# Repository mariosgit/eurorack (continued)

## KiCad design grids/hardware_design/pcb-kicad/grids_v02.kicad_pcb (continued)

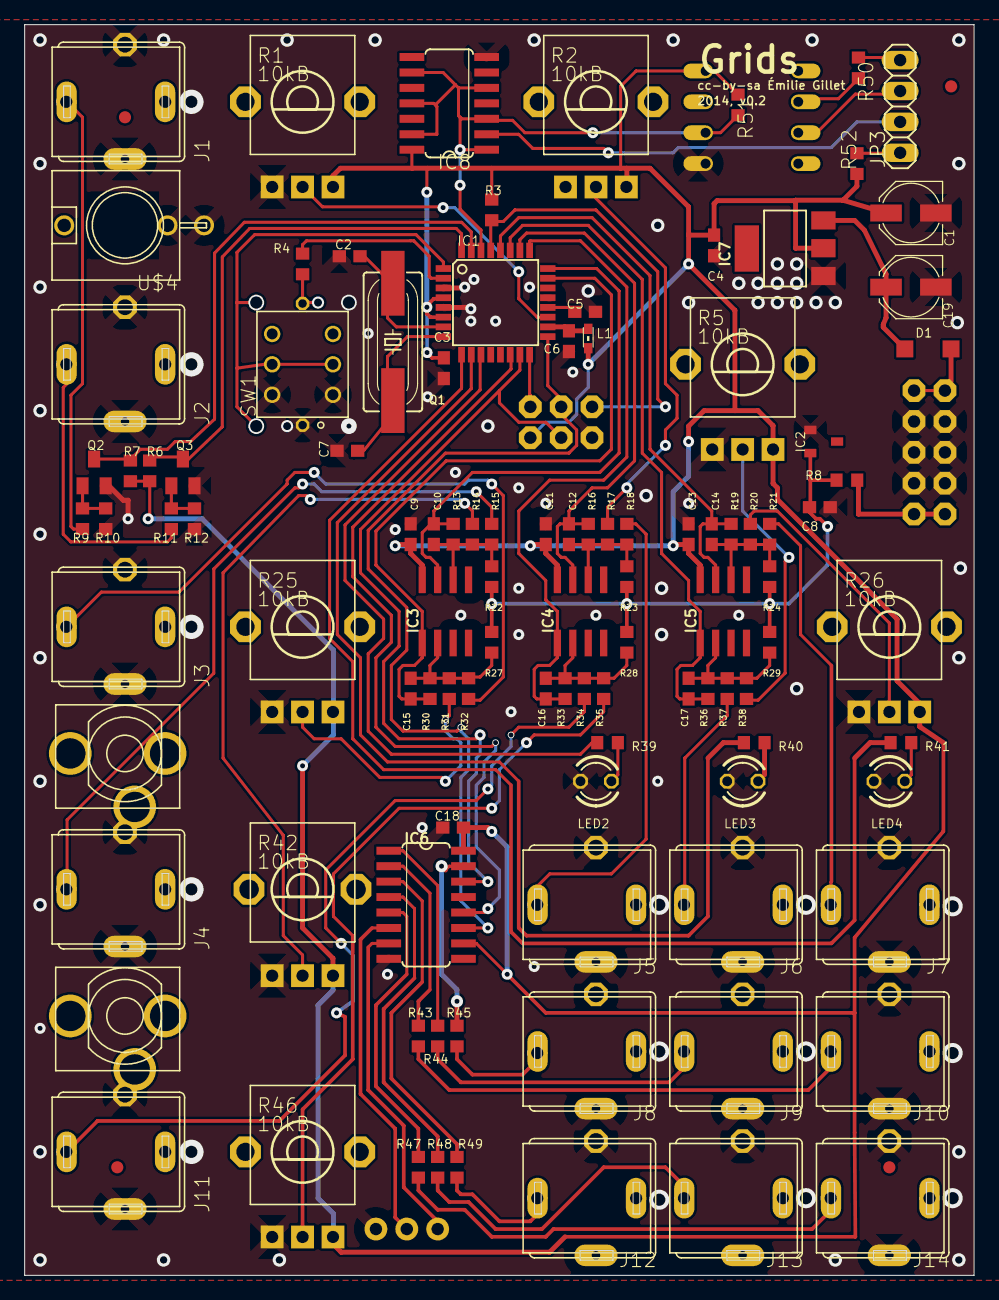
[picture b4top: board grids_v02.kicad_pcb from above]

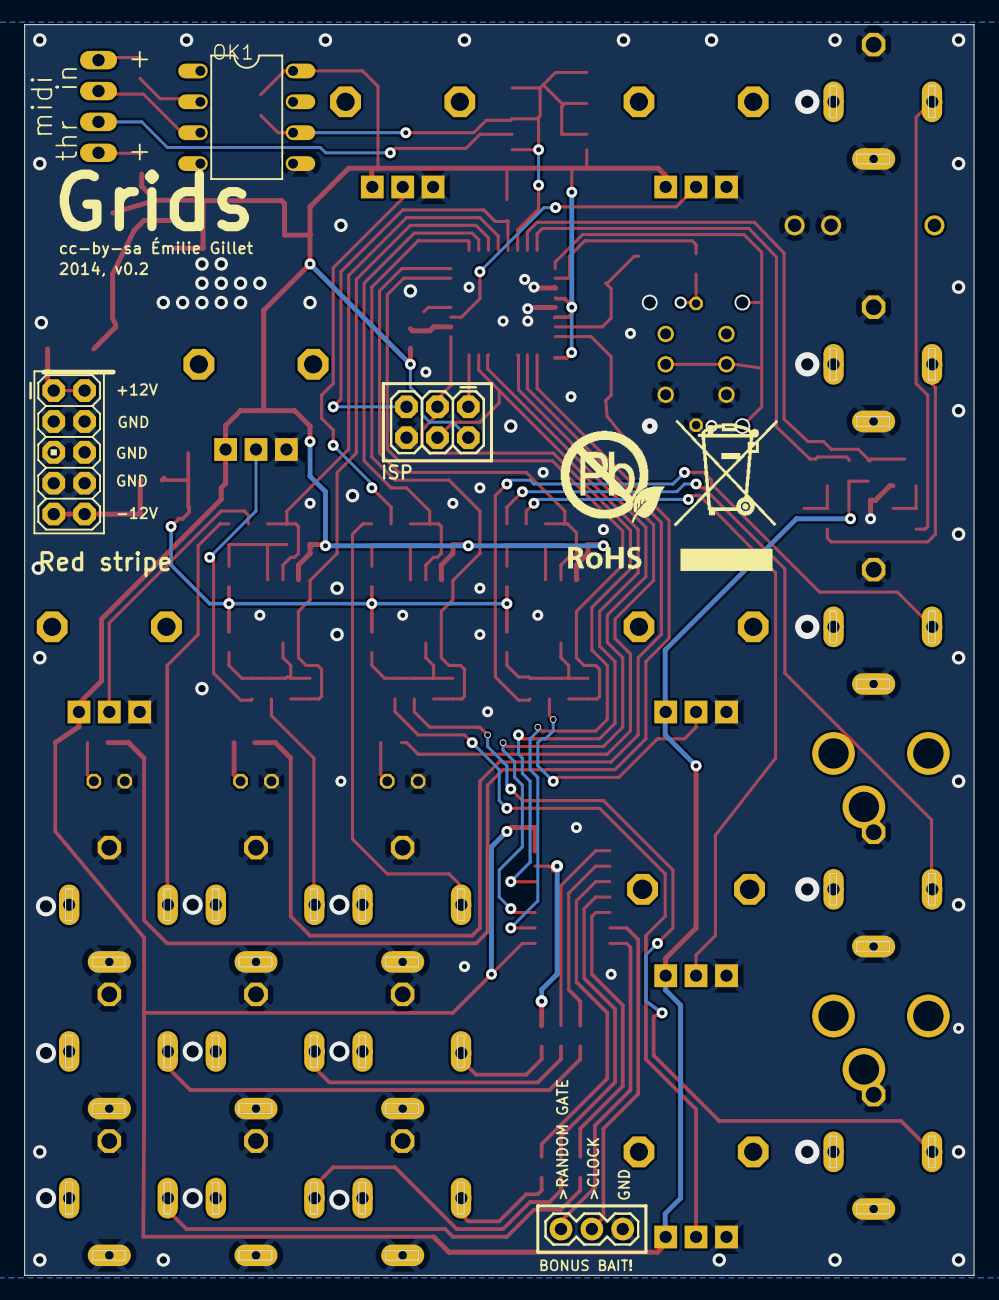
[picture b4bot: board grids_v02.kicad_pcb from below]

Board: 2 copper layers, 78.1 x 102.9 mm, 115 parts (5 on the bottom side), 75 nets.

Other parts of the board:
U$2: ROHS_BIG

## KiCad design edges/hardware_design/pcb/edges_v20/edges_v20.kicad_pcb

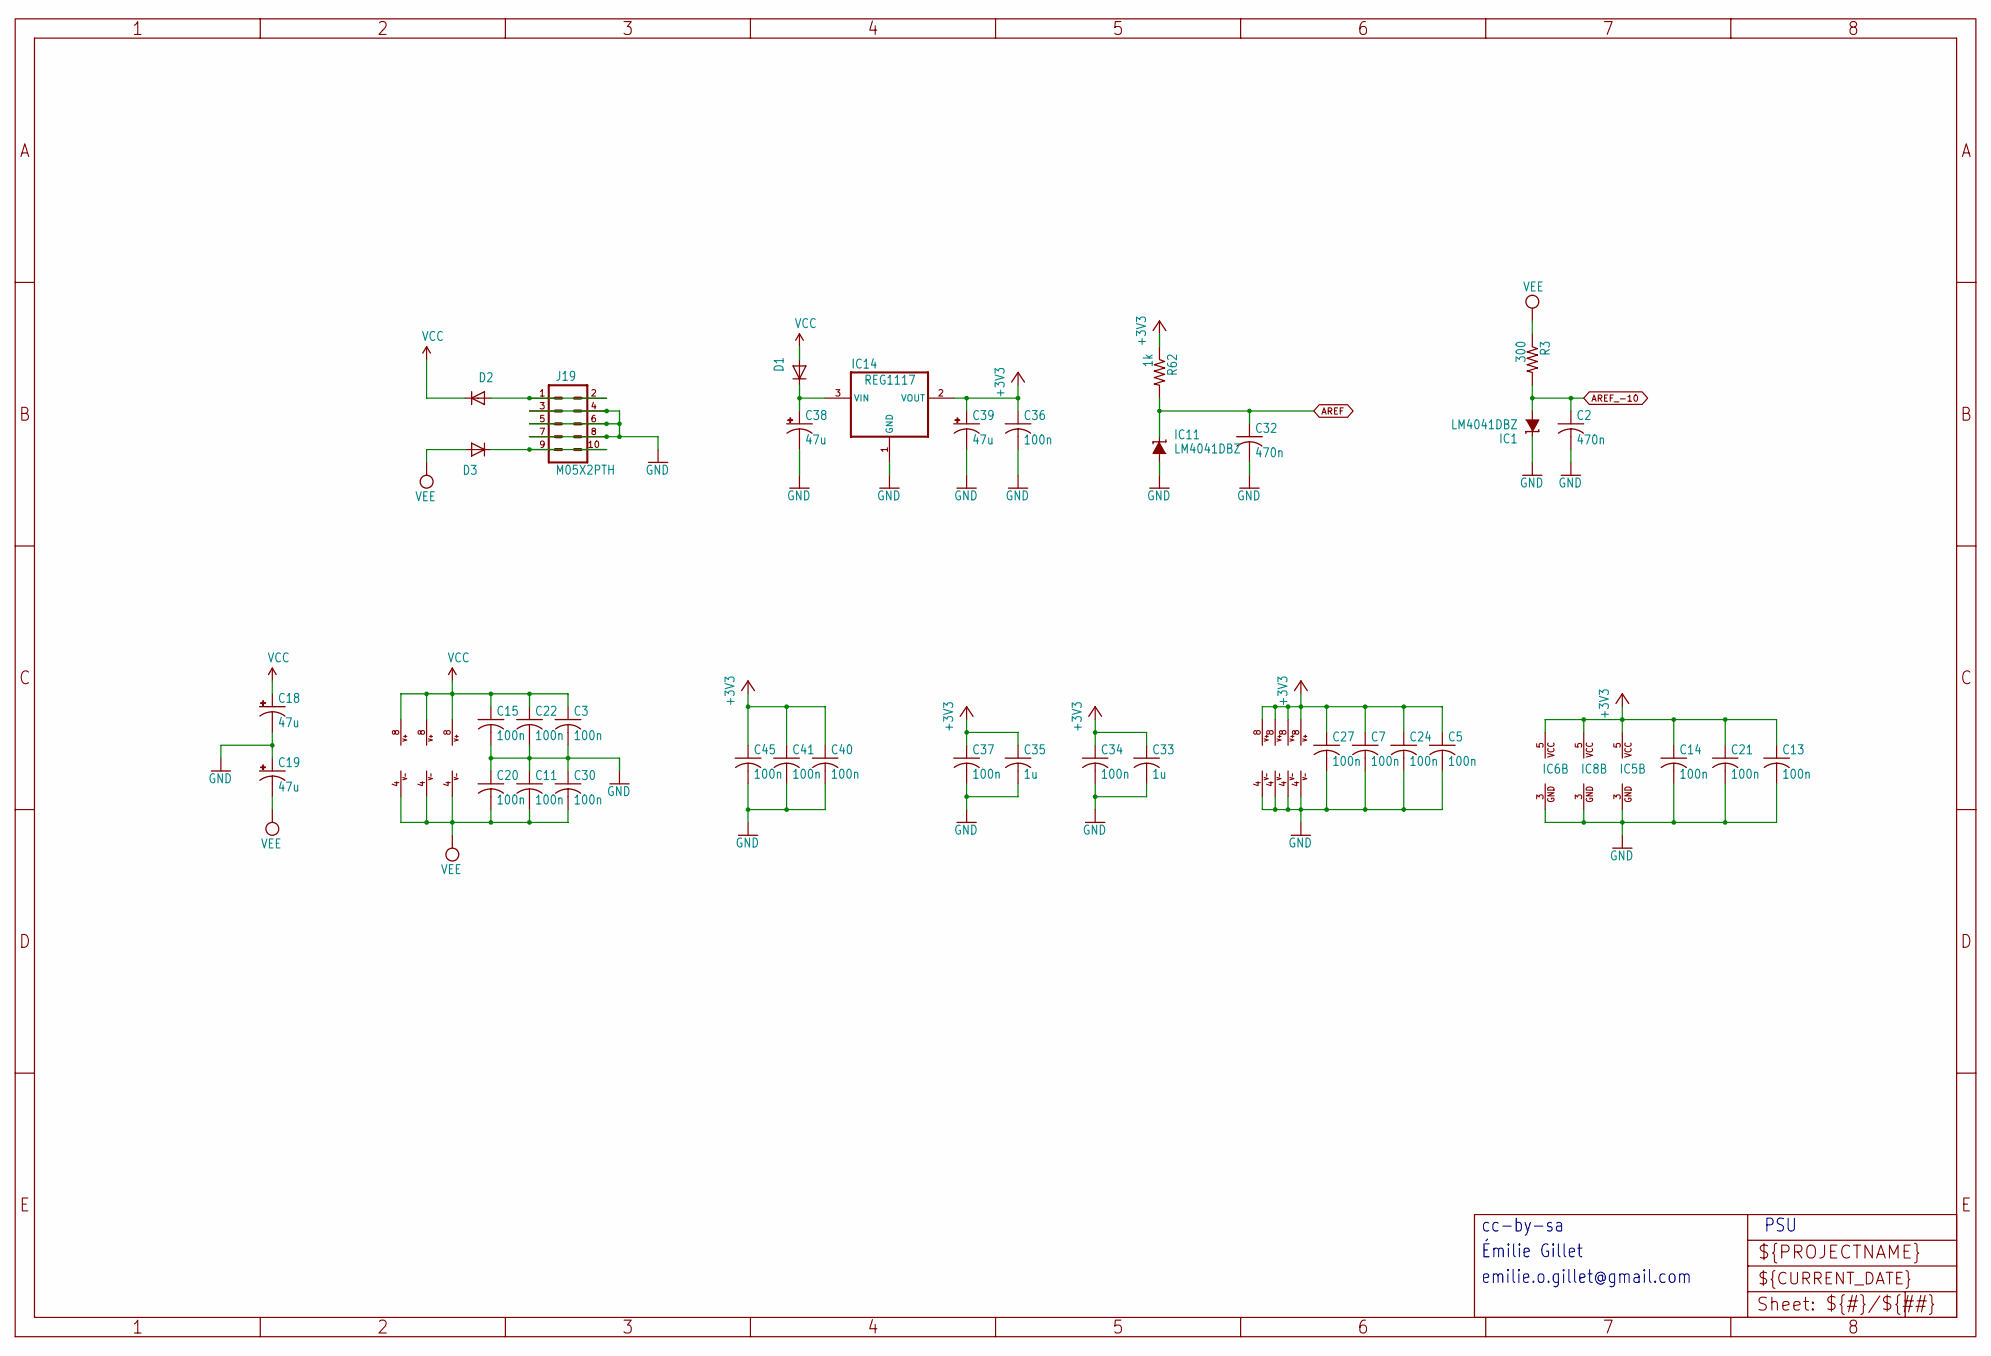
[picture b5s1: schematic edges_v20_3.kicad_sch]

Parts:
C2, C32: 470n; C0603
C3, C5, C7, C11, C13, C14, C15, C20, C21, C22, C24, C27, C30, C34, C36, C37, C40, C41, C45: 100n; C0603
C18, C19, C38, C39: 47u; PANASONIC_D
C33, C35: 1u; C0603
D1, D2, D3: 1N5819HW; SOD123
IC1, IC11: LM4041DBZ; DBZ_R-PDSO-G3
IC2, IC3, IC4, IC7, IC9, IC10, IC12: TL072D; SO08
IC5: 741G125DBV; SOT23-5
IC6, IC8: 741G86DBV; SOT23-5
IC14: REG1117; SOT223
J19: M05X2PTH; AVR_ICSP
R3: 300; R0603
R62: 1k; R0603

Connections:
+3V3: C5.1, C7.1, C13.1, C14.1, C21.1, C24.1, C27.1, C33.1, C34.1, C35.1, C36.1, C37.1, C39.+, C40.1, C41.1, C45.1, IC3.8 (V+), IC4.8 (V+), IC5.5 (VCC), IC6.5 (VCC), IC8.5 (VCC), IC10.8 (V+), IC12.8 (V+), IC14.2 (VOUT), R62.1; also elsewhere on the board
AREF: C32.1, IC11.1 (C), R62.2; also elsewhere on the board
AREF_-10: C2.1, IC1.2 (A), R3.2; also elsewhere on the board
GND: C2.2, C3.2, C5.2, C7.2, C11.1, C13.2, C14.2, C15.2, C18.-, C19.+, C20.1, C21.2, C22.2, C24.2, C27.2, C30.1, C32.2, C33.2, C34.2, C35.2, C36.2, C37.2, C38.-, C39.-, C40.2, C41.2, C45.2, IC1.1 (C), IC3.4 (V-), IC4.4 (V-), IC5.3 (GND), IC6.3 (GND), IC8.3 (GND), IC10.4 (V-), IC11.2 (A), IC12.4 (V-), IC14.1 (GND), J19.3, J19.4, J19.5, J19.6, J19.7, J19.8; also elsewhere on the board
unnamed: D2.A, J19.1, J19.2
unnamed: D3.C, J19.9, J19.10
unnamed: C38.+, D1.C, IC14.3 (VIN)
VCC: C3.1, C15.1, C18.+, C22.1, D1.A, D2.C, IC2.8 (V+), IC7.8 (V+), IC9.8 (V+); also elsewhere on the board
VEE: C11.2, C19.-, C20.2, C30.2, D3.A, IC2.4 (V-), IC7.4 (V-), IC9.4 (V-), R3.1

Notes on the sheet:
PSU
Émilie Gillet
cc-by-sa
emilie.o.gillet@gmail.com

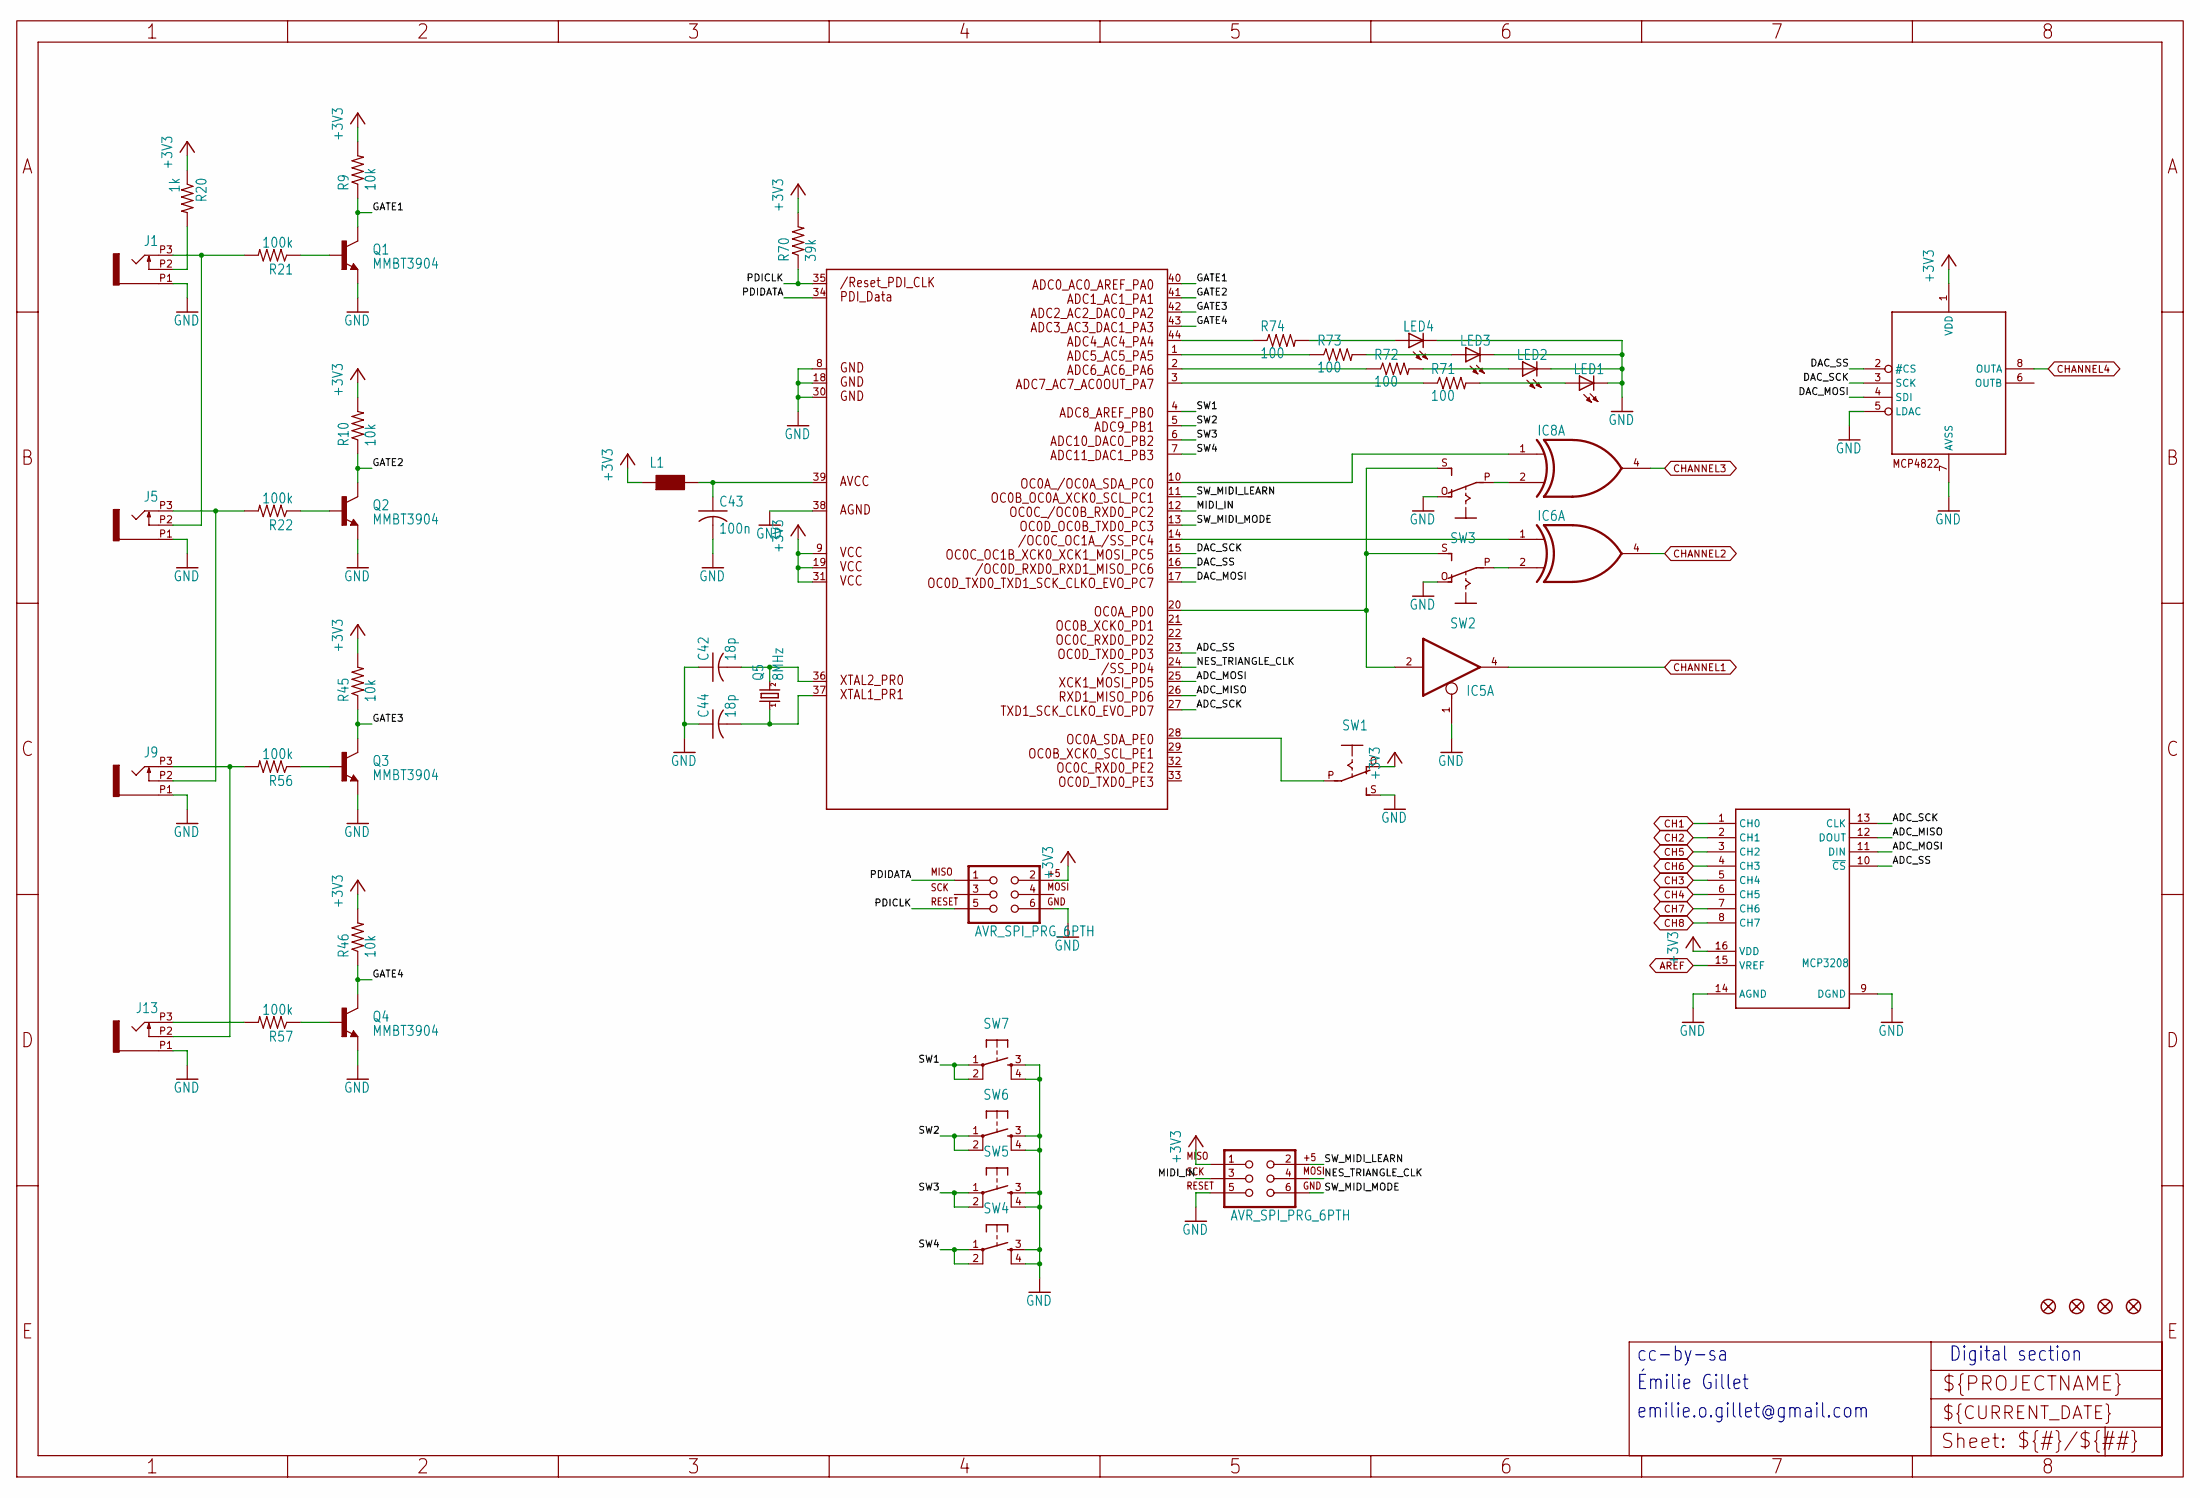
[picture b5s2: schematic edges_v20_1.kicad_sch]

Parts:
C42, C44: 18p; C0603
C43: 100n; C0603
IC5: 741G125DBV; SOT23-5
IC6, IC8: 741G86DBV; SOT23-5
IC13: MCP3208; SO16
IC15: MCP4822SO08; SO08
IC16: AVR_XMEGA_A4_44A; TQFP44
J1, J5, J9, J13: PJ301_THONKICONN6; WQP_PJ_301M6
J18, J20: AVR_SPI_PRG_6PTH; 2X3
JP1, JP2, JP3, JP4: FIDUCIAL1X2; FIDUCIAL-1X2
L1: WE-CBF_0603; 0603
LED1, LED2, LED3, LED4: LED3MM
Q1, Q2, Q3, Q4: MMBT3904; SOT23-BEC
Q5: 8MHz; HC49U70
R9, R10, R45, R46: 10k; R0603
R20: 1k; R0603
R21, R22, R56, R57: 100k; R0603
R70: 39k; R0603
R71, R72, R73, R74: 100; R0603
SW1, SW2, SW3: S-ON-ONSMALL_SLIDE; ES_100SP1T6B11M2QEH_SMALL
SW4, SW5, SW6, SW7: TAC_SWITCHPTH; TACTILE-PTH

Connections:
+3V3: IC13.16 (VDD), IC15.1 (VDD), IC16.9 (VCC1), IC16.19 (VCC2), IC16.31 (VCC3), J18.1, J20.2, L1.1, R9.2, R10.2, R20.1, R45.2, R46.2, R70.2, SW1.O; also elsewhere on the board
/edges_v20_1/ADC_MISO: IC13.12 (DOUT), IC16.26 (PD6)
/edges_v20_1/ADC_MOSI: IC13.11 (DIN), IC16.25 (PD5)
/edges_v20_1/ADC_SCK: IC13.13 (CLK), IC16.27 (PD7)
/edges_v20_1/ADC_SS: IC13.10 (~CS), IC16.23 (PD3)
/edges_v20_1/DAC_MOSI: IC15.4 (SDI), IC16.17 (PC7)
/edges_v20_1/DAC_SCK: IC15.3 (SCK), IC16.15 (PC5)
/edges_v20_1/DAC_SS: IC15.2 (#CS), IC16.16 (PC6)
/edges_v20_1/GATE1: IC16.40 (PA0), Q1.C, R9.1
/edges_v20_1/GATE2: IC16.41 (PA1), Q2.C, R10.1
/edges_v20_1/GATE3: IC16.42 (PA2), Q3.C, R45.1
/edges_v20_1/GATE4: IC16.43 (PA3), Q4.C, R46.1
/edges_v20_1/MIDI_IN: IC16.12 (PC2), J18.3
/edges_v20_1/NES_TRIANGLE_CLK: IC16.24 (PD4), J18.4
/edges_v20_1/PDICLK: IC16.35 (RESET), J20.5, R70.1
/edges_v20_1/PDIDATA: IC16.34 (PDI_DATA), J20.1
/edges_v20_1/SW1: IC16.4 (PB0), SW7.1, SW7.2
/edges_v20_1/SW2: IC16.5 (PB1), SW6.1, SW6.2
/edges_v20_1/SW3: IC16.6 (PB2), SW5.1, SW5.2
/edges_v20_1/SW4: IC16.7 (PB3), SW4.1, SW4.2
/edges_v20_1/SW_MIDI_LEARN: IC16.11 (PC1), J18.2
/edges_v20_1/SW_MIDI_MODE: IC16.13 (PC3), J18.6
AREF: IC13.15 (VREF); also elsewhere on the board
CH1: IC13.1 (CH0); also elsewhere on the board
CH2: IC13.2 (CH1); also elsewhere on the board
CH3: IC13.5 (CH4); also elsewhere on the board
CH4: IC13.6 (CH5); also elsewhere on the board
CH5: IC13.3 (CH2); also elsewhere on the board
CH6: IC13.4 (CH3); also elsewhere on the board
CH7: IC13.7 (CH6); also elsewhere on the board
CH8: IC13.8 (CH7); also elsewhere on the board
CHANNEL1: IC5.4 (O); also elsewhere on the board
CHANNEL2: IC6.4 (O); also elsewhere on the board
CHANNEL3: IC8.4 (O); also elsewhere on the board
CHANNEL4: IC15.8 (OUTA); also elsewhere on the board
GND: C42.1, C43.2, C44.1, IC5.1 (OE), IC13.9 (DGND), IC13.14 (AGND), IC15.5 (LDAC), IC15.7 (AVSS), IC16.8 (GND1), IC16.18 (GND2), IC16.30 (GND3), IC16.38 (AGND), J1.P1 (1), J5.P1 (1), J9.P1 (1), J13.P1 (1), J18.5, J20.6, LED1.K (C), LED2.K (C), LED3.K (C), LED4.K (C), Q1.E, Q2.E, Q3.E, Q4.E, SW1.S, SW2.O, SW3.O, SW4.3, SW4.4, SW5.3, SW5.4, SW6.3, SW6.4, SW7.3, SW7.4; also elsewhere on the board
unnamed: IC6.2 (I1), SW2.P
unnamed: IC8.2 (I1), SW3.P
unnamed: C43.1, IC16.39 (AVCC), L1.2
unnamed: IC16.44 (PA4), R74.1
unnamed: IC16.1 (PA5), R73.1
unnamed: IC16.2 (PA6), R72.1
unnamed: IC16.3 (PA7), R71.1
unnamed: IC8.1 (I0), IC16.10 (PC0)
unnamed: IC6.1 (I0), IC16.14 (PC4)
unnamed: IC5.2 (I), IC16.20 (PD0), SW2.S, SW3.S
unnamed: IC16.28 (PE0), SW1.P
unnamed: C42.2, IC16.36 (PR0), Q5.2
unnamed: C44.2, IC16.37 (PR1), Q5.1
unnamed: J1.P2 (2), R20.2
unnamed: J1.P3 (3), J5.P2 (2), R21.2
unnamed: J5.P3 (3), J9.P2 (2), R22.2
unnamed: J9.P3 (3), J13.P2 (2), R56.2
unnamed: J13.P3 (3), R57.2
unnamed: LED1.A, R71.2
unnamed: LED2.A, R72.2
unnamed: LED3.A, R73.2
unnamed: LED4.A, R74.2
unnamed: Q1.B, R21.1
unnamed: Q2.B, R22.1
unnamed: Q3.B, R56.1
unnamed: Q4.B, R57.1

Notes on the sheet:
cc-by-sa
emilie.o.gillet@gmail.com
Digital section
Émilie Gillet

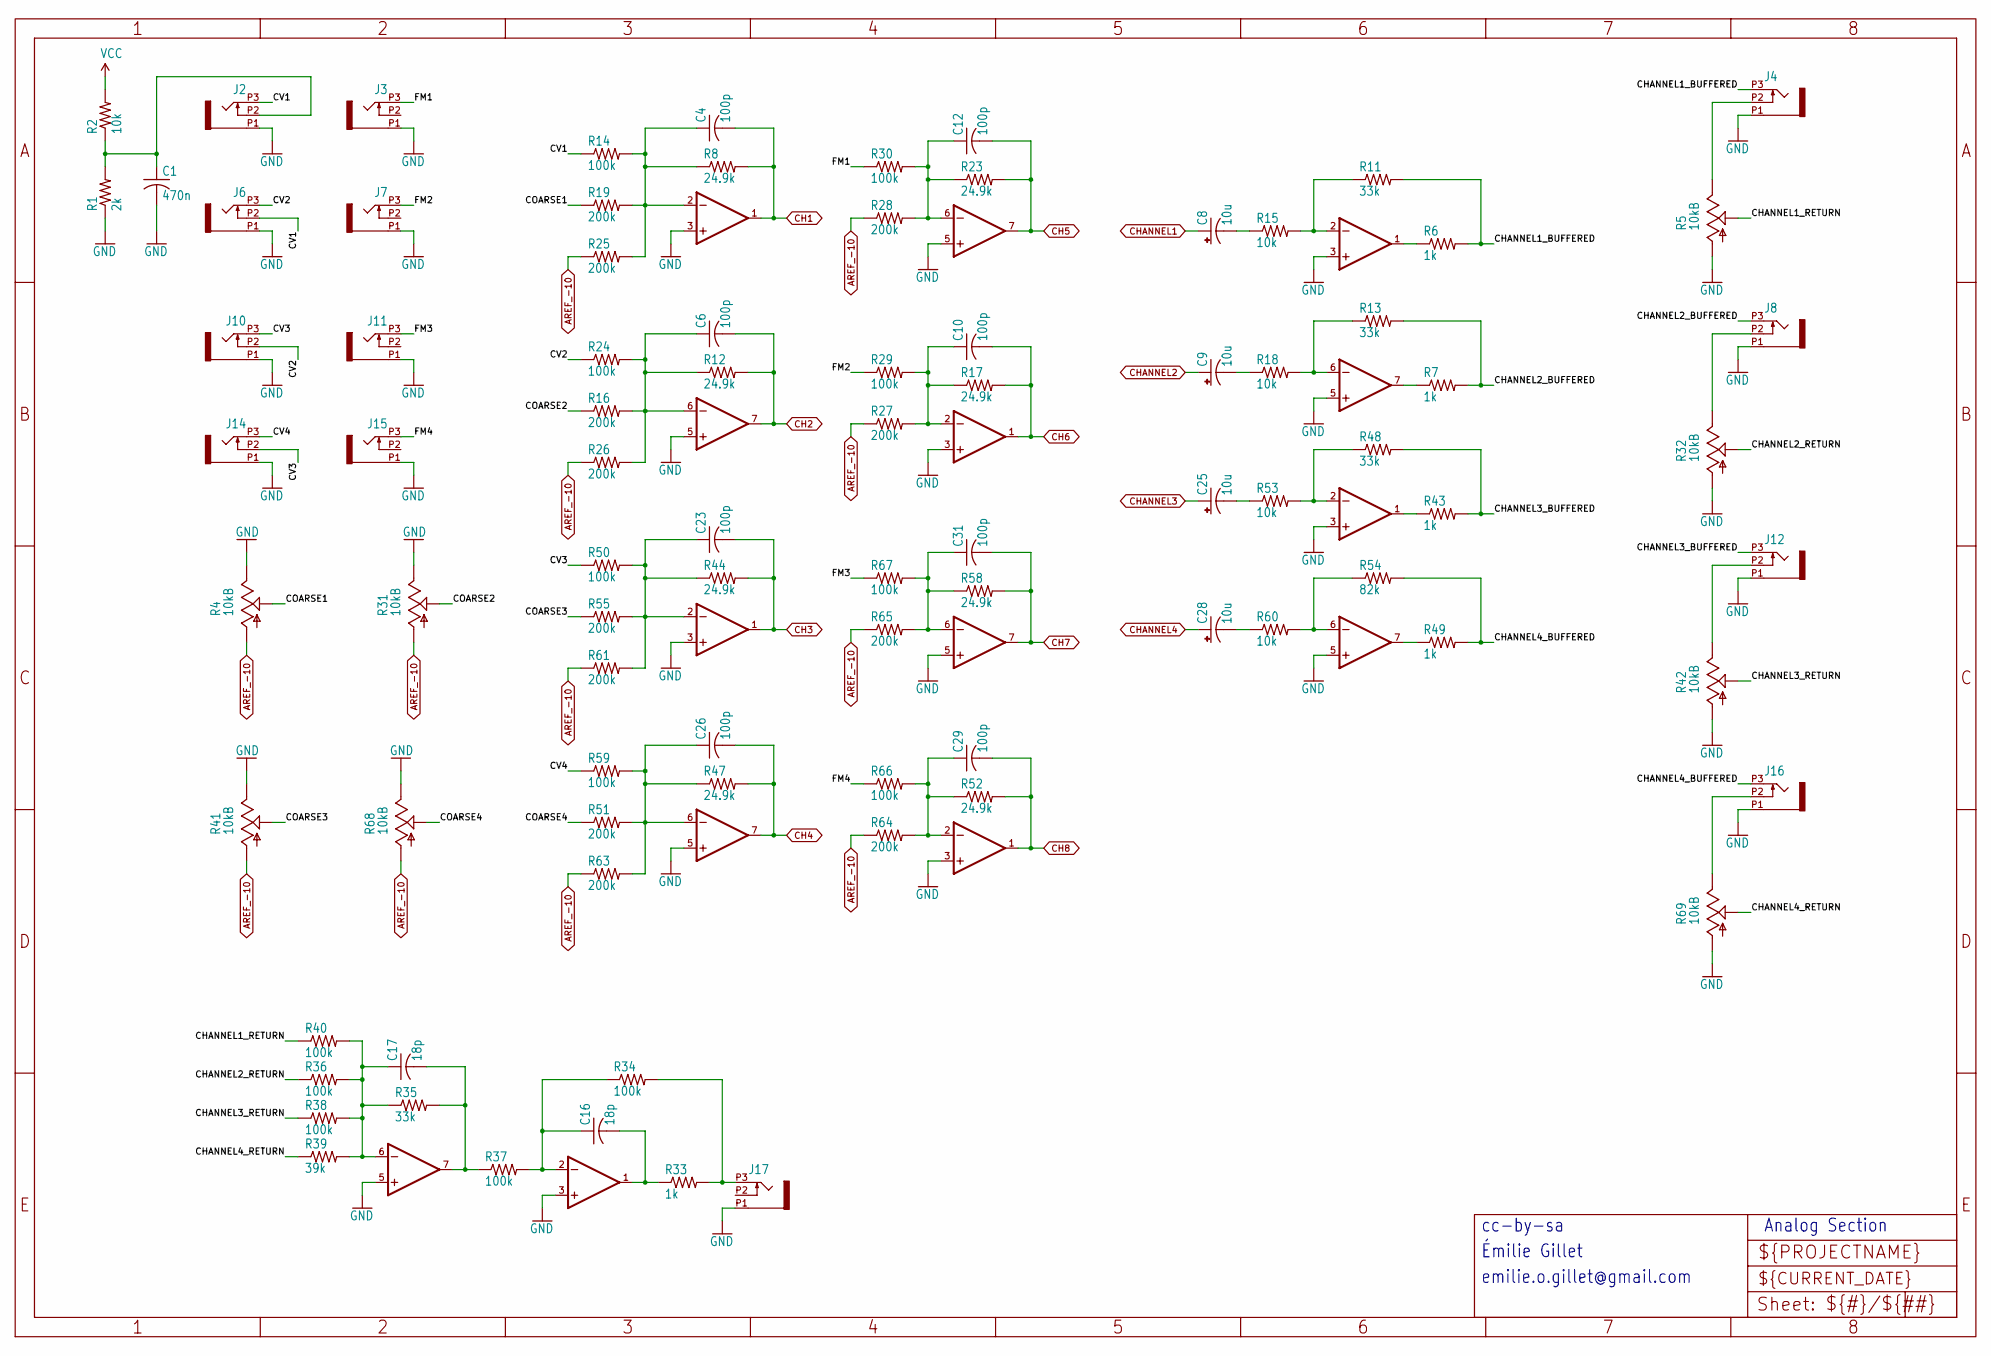
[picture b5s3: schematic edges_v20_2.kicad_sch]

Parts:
C1: 470n; C0603
C4, C6, C10, C12, C23, C26, C29, C31: 100p; C0603
C8, C9, C25, C28: 10u; PANASONIC_B
C16, C17: 18p; C0603
IC2, IC3, IC4, IC7, IC9, IC10, IC12: TL072D; SO08
J2, J3, J4, J6, J7, J8, J10, J11, J12, J14, J15, J16, J17: PJ301_THONKICONN6; WQP_PJ_301M6
R1: 2k; R0603
R2, R15, R18, R53, R60: 10k; R0603
R4, R5, R31, R32, R41, R42, R68, R69: 10kB; ALPS_POT_VERTICAL_PS
R6, R7, R33, R43, R49: 1k; R0603
R8, R12, R17, R23, R44, R47, R52, R58: 24.9k; R0603
R11, R13, R35, R48: 33k; R0603
R14, R24, R29, R30, R34, R36, R37, R38, R40, R50, R59, R66, R67: 100k; R0603
R16, R19, R25, R26, R27, R28, R51, R55, R61, R63, R64, R65: 200k; R0603
R39: 39k; R0603
R54: 82k; R0603

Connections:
/edges_v20_2/CHANNEL1_BUFFERED: J4.P3 (3), R6.2, R11.2
/edges_v20_2/CHANNEL1_RETURN: R5.P$2 (S), R40.1
/edges_v20_2/CHANNEL2_BUFFERED: J8.P3 (3), R7.2, R13.2
/edges_v20_2/CHANNEL2_RETURN: R32.P$2 (S), R36.1
/edges_v20_2/CHANNEL3_BUFFERED: J12.P3 (3), R43.2, R48.2
/edges_v20_2/CHANNEL3_RETURN: R38.1, R42.P$2 (S)
/edges_v20_2/CHANNEL4_BUFFERED: J16.P3 (3), R49.2, R54.2
/edges_v20_2/CHANNEL4_RETURN: R39.1, R69.P$2 (S)
/edges_v20_2/COARSE1: R4.P$2 (S), R19.1
/edges_v20_2/COARSE2: R16.1, R31.P$2 (S)
/edges_v20_2/COARSE3: R41.P$2 (S), R55.1
/edges_v20_2/COARSE4: R51.1, R68.P$2 (S)
/edges_v20_2/CV1: J2.P3 (3), J6.P2 (2), R14.1
/edges_v20_2/CV2: J6.P3 (3), J10.P2 (2), R24.1
/edges_v20_2/CV3: J10.P3 (3), J14.P2 (2), R50.1
/edges_v20_2/CV4: J14.P3 (3), R59.1
/edges_v20_2/FM1: J3.P3 (3), R30.1
/edges_v20_2/FM2: J7.P3 (3), R29.1
/edges_v20_2/FM3: J11.P3 (3), R67.1
/edges_v20_2/FM4: J15.P3 (3), R66.1
AREF_-10: R4.P$3 (A), R25.1, R26.1, R27.1, R28.1, R31.P$3 (A), R41.P$3 (A), R61.1, R63.1, R64.1, R65.1, R68.P$3 (A); also elsewhere on the board
CH1: C4.2, IC3.1 (OUT), R8.2; also elsewhere on the board
CH2: C6.2, IC3.7 (OUT), R12.2; also elsewhere on the board
CH3: C23.2, IC10.1 (OUT), R44.2; also elsewhere on the board
CH4: C26.2, IC10.7 (OUT), R47.2; also elsewhere on the board
CH5: C12.2, IC4.7 (OUT), R23.2; also elsewhere on the board
CH6: C10.2, IC4.1 (OUT), R17.2; also elsewhere on the board
CH7: C31.2, IC12.7 (OUT), R58.2; also elsewhere on the board
CH8: C29.2, IC12.1 (OUT), R52.2; also elsewhere on the board
CHANNEL1: C8.+; also elsewhere on the board
CHANNEL2: C9.+; also elsewhere on the board
CHANNEL3: C25.+; also elsewhere on the board
CHANNEL4: C28.+; also elsewhere on the board
GND: C1.2, IC2.3 (+IN), IC2.5 (+IN), IC3.3 (+IN), IC3.5 (+IN), IC4.3 (+IN), IC4.5 (+IN), IC7.3 (+IN), IC7.5 (+IN), IC9.3 (+IN), IC9.5 (+IN), IC10.3 (+IN), IC10.5 (+IN), IC12.3 (+IN), IC12.5 (+IN), J2.P1 (1), J3.P1 (1), J4.P1 (1), J6.P1 (1), J7.P1 (1), J8.P1 (1), J10.P1 (1), J11.P1 (1), J12.P1 (1), J14.P1 (1), J15.P1 (1), J16.P1 (1), J17.P1 (1), R1.1, R4.P$1 (E), R5.P$3 (A), R31.P$1 (E), R32.P$3 (A), R41.P$1 (E), R42.P$3 (A), R68.P$1 (E), R69.P$3 (A); also elsewhere on the board
unnamed: C8.-, R15.1
unnamed: C9.-, R18.1
unnamed: C25.-, R53.1
unnamed: C28.-, R60.1
unnamed: IC2.2 (-IN), R11.1, R15.2
unnamed: IC2.1 (OUT), R6.1
unnamed: IC2.6 (-IN), R13.1, R18.2
unnamed: IC2.7 (OUT), R7.1
unnamed: C4.1, IC3.2 (-IN), R8.1, R14.2, R19.2, R25.2
unnamed: C6.1, IC3.6 (-IN), R12.1, R16.2, R24.2, R26.2
unnamed: C10.1, IC4.2 (-IN), R17.1, R27.2, R29.2
unnamed: C12.1, IC4.6 (-IN), R23.1, R28.2, R30.2
unnamed: C16.1, IC7.2 (-IN), R34.1, R37.2
unnamed: C16.2, IC7.1 (OUT), R33.1
unnamed: C17.1, IC7.6 (-IN), R35.1, R36.2, R38.2, R39.2, R40.2
unnamed: C17.2, IC7.7 (OUT), R35.2, R37.1
unnamed: IC9.2 (-IN), R48.1, R53.2
unnamed: IC9.1 (OUT), R43.1
unnamed: IC9.6 (-IN), R54.1, R60.2
unnamed: IC9.7 (OUT), R49.1
unnamed: C23.1, IC10.2 (-IN), R44.1, R50.2, R55.2, R61.2
unnamed: C26.1, IC10.6 (-IN), R47.1, R51.2, R59.2, R63.2
unnamed: C29.1, IC12.2 (-IN), R52.1, R64.2, R66.2
unnamed: C31.1, IC12.6 (-IN), R58.1, R65.2, R67.2
unnamed: C1.1, J2.P2 (2), R1.2, R2.1
unnamed: J4.P2 (2), R5.P$1 (E)
unnamed: J8.P2 (2), R32.P$1 (E)
unnamed: J12.P2 (2), R42.P$1 (E)
unnamed: J16.P2 (2), R69.P$1 (E)
unnamed: J17.P3 (3), R33.2, R34.2
VCC: R2.2; also elsewhere on the board

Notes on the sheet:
emilie.o.gillet@gmail.com
Analog Section
cc-by-sa
Émilie Gillet

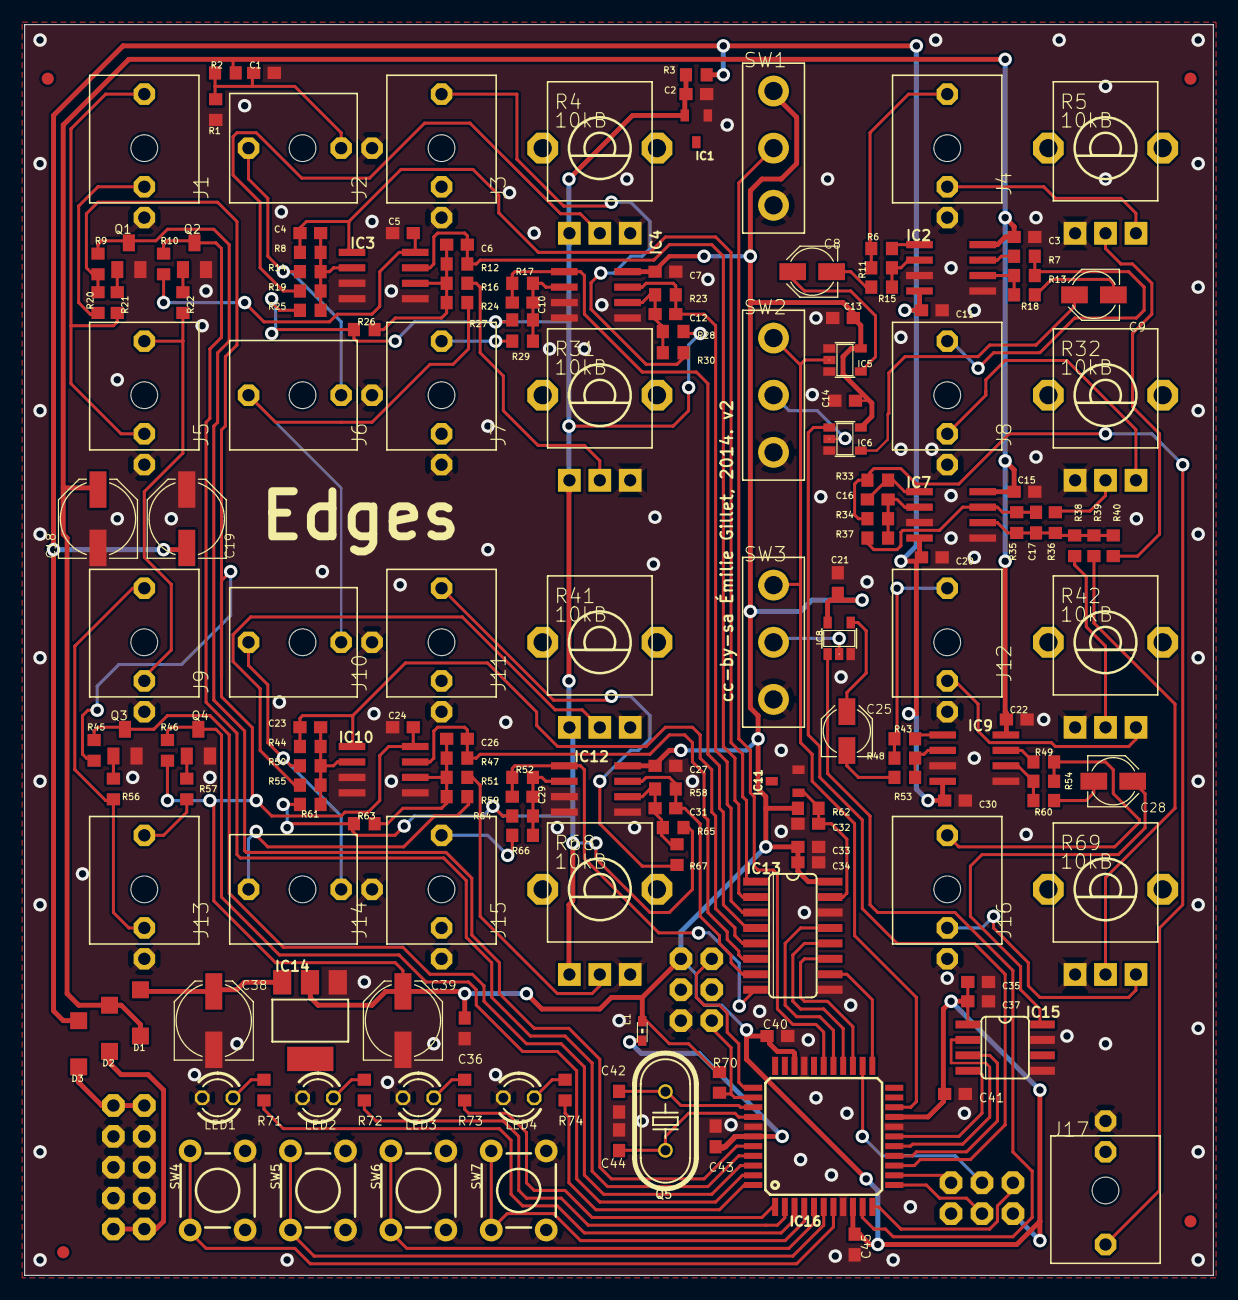
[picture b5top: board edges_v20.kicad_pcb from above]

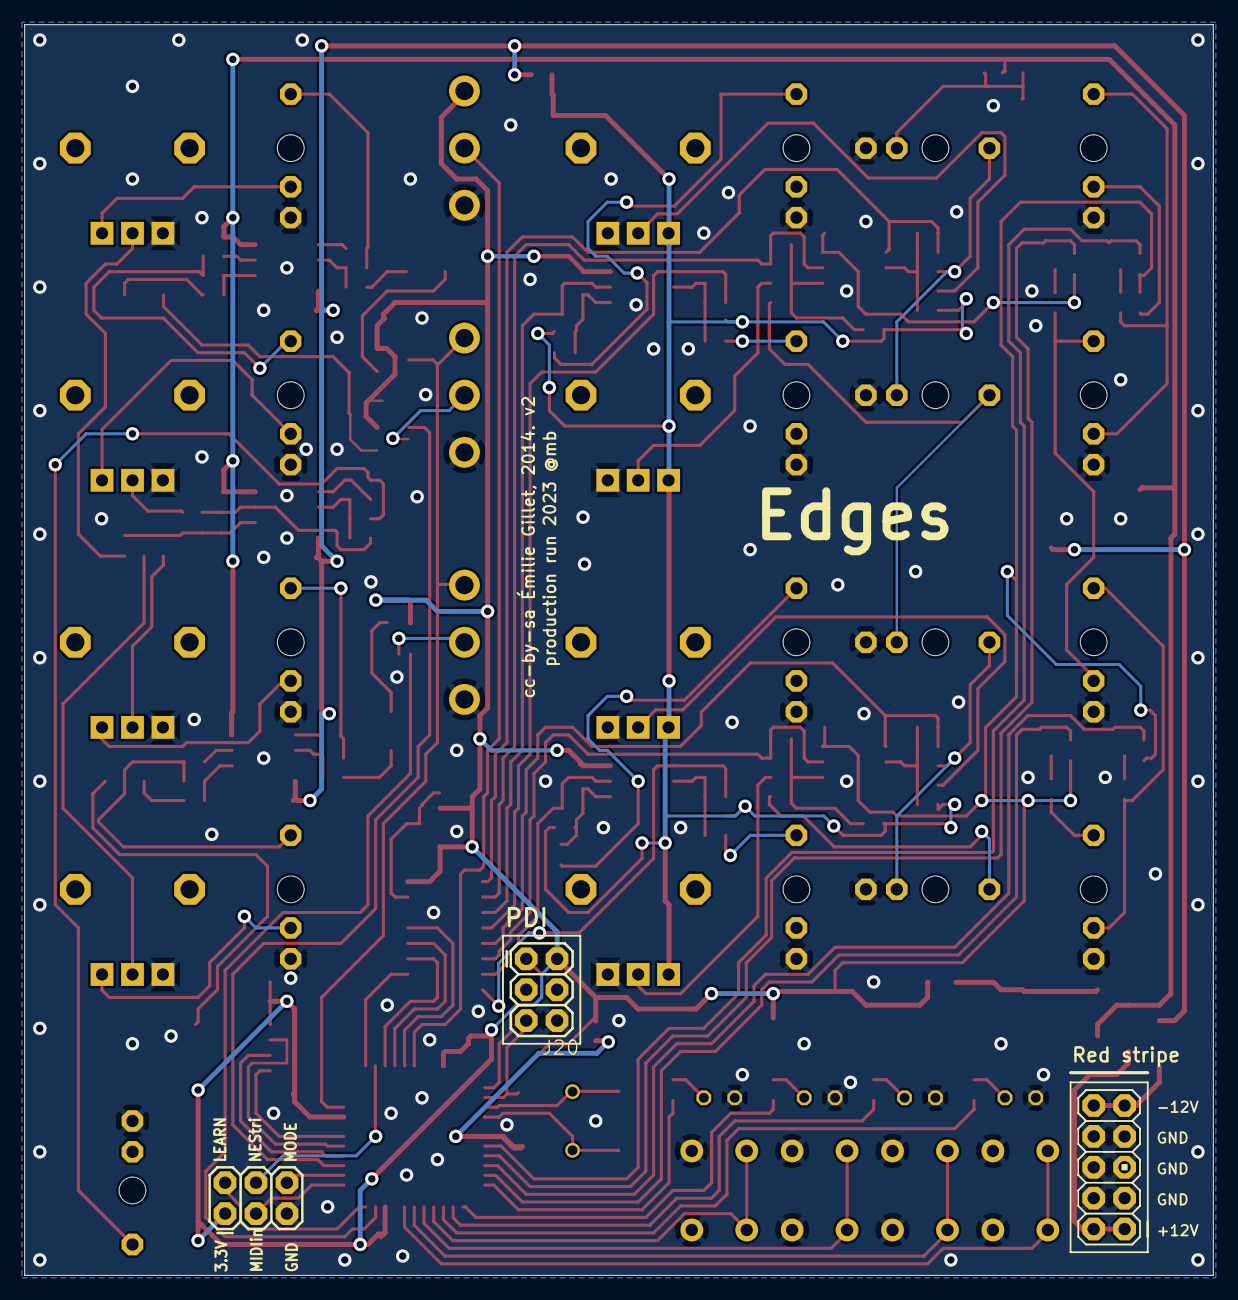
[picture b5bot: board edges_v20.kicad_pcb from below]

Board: 2 copper layers, 97.8 x 102.9 mm, 179 parts (3 on the bottom side), 118 nets.
